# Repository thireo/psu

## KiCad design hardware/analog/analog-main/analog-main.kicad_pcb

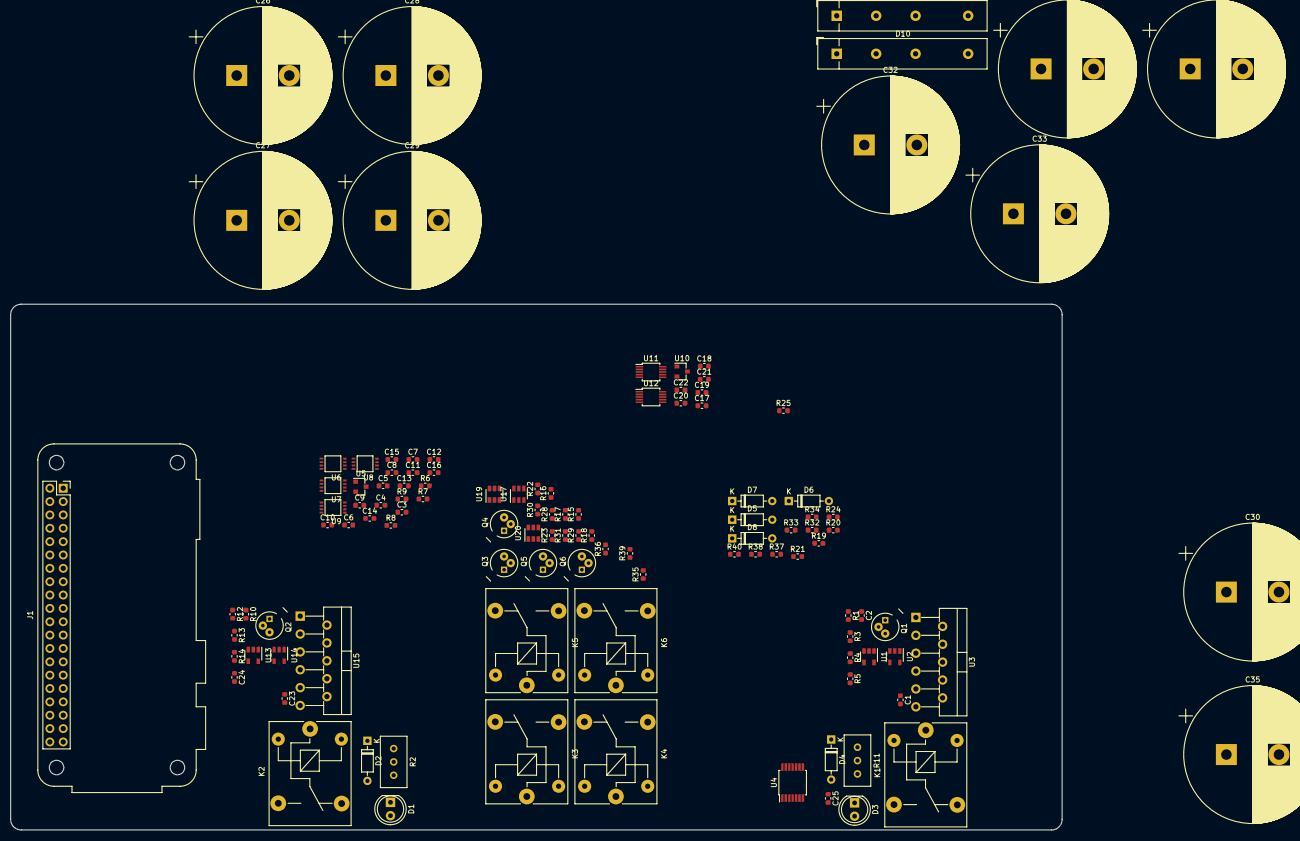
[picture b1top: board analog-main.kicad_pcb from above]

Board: 2 copper layers, 200.0 x 100.0 mm, 114 parts (0 on the bottom side), 61 nets, no tracks yet.

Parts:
C1, C2, C5, C8, C9, C10, C15, C16, C17, C18, C19, C20, C21, C22, C23, C24, C25: 100n; C_0603_1608Metric
C3, C4, C11, C12: 100n / 100p; C_0603_1608Metric
C6, C7, C13, C14: 4u7; C_0603_1608Metric
C26, C27, C28, C29, C30, C31, C32, C33, C34, C35: 4700u; CP_Radial_D26.0mm_P10.00mm_SnapIn
D1, D3: TEMP_LED; LED_D5.0mm
D2, D4, D5, D6, D7, D8: D_Zener; D_DO-35_SOD27_P7.62mm_Horizontal
D9, D10: D_Bridge_+-AA; Diode_Bridge_32.0x5.6x17.0mm_P10.0mm_P7.5mm
J1: Raspberry_Pi_2_3; Raspberry_Pi_Zero_Socketed_THT_FaceDown_MountingHoles
K1, K2, K3, K4, K5, K6: SANYOU_SRD_Form_C; Relay_SPDT_SANYOU_SRD_Series_Form_C
Q1, Q2, Q3, Q4, Q5, Q6: 2N2222; TO-18-3
R1, R4, R10, R13, R15, R17, R28, R30, R36, R39: 1k; R_0603_1608Metric
R2, R11: 10k POT; Potentiometer_Bourns_3296W_Vertical
R3, R12: >250; R_0603_1608Metric
R5, R6, R7, R8, R9, R14, R16, R18, R29, R31: 10k; R_0603_1608Metric
R19, R32: 100m 1%; R_0603_1608Metric
R20, R33: 5R 1%; R_0603_1608Metric
R21, R22, R34: 10k 1%; R_0603_1608Metric
R23, R25: 1k 1%; R_0603_1608Metric
R24: 33k 1%; R_0603_1608Metric
R35: 100R; R_0603_1608Metric
R37: 6k8 1%; R_0603_1608Metric
R38: 2k2 1%; R_0603_1608Metric
R40: 3k 1%; R_0603_1608Metric
U1, U2, U13, U14: LMV321; SOT-23-5
U3, U15: OPA549; TO-220-11_P3.4x5.08mm_StaggerOdd_Lead4.85mm_Vertical
U4: 74HCT04; TSSOP-14_4.4x5mm_P0.65mm
U5, U10: MCP1525-TT; SOT-23
U6, U7, U8, U9: MAX5216; uMAX8
U11, U12: MCP3301; MSOP-10_3x3mm_P0.5mm
U17, U19, U20: MAX4239AUT; SOT-23-6

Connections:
+1V8: C19.1, C21.1, U11.2, U12.2
+3V3: C20.1, C22.1, U11.10, U12.10
+4V: C10.1, U5.2, U6.1, U7.1, U8.1, U9.1
+5C: C1.1, C2.1, C6.1, C7.1, C8.2, C9.2, C13.1, C14.1, C15.2, C16.2, C23.1, C24.1, C25.1, U1.5, U2.5, U4.14, U6.7, U7.7, U8.7, U9.7, U13.5, U14.5, U17.6, U19.6, U20.6
+5V: C5.1, C17.1, D2.1, D4.1, D5.1, D6.1, D7.1, D8.1, K1.2, K2.2, K3.2, K4.2, K5.2, K6.2, U5.1, U10.1
+36V: U3.10, U3.11, U15.10, U15.11
-5V: U19.2, U20.2
/Analog to Digital/AIN0+: U11.3, U17.1
/Analog to Digital/AIN1+: R40.1, U12.3, U20.1
/Analog to Digital/MISO: U11.7, U12.7
/Analog to Digital/MOSI: U6.4, U7.4, U8.4, U9.4, U11.9, U12.9
/Analog to Digital/SCK: U6.3, U7.3, U8.3, U9.3, U11.8, U12.8
/Current Measurements/OUT_0+: K1.3, K3.1
/Current Measurements/OUT_1+: K2.3, K5.1
/Digital to Analog/DAC_OUT_0: U2.3, U2.4, U3.8, U7.6
/Digital to Analog/DAC_OUT_1: U1.3, U1.4, U3.4, U6.6
/Digital to Analog/DAC_OUT_2: U9.6, U14.3, U14.4, U15.8
/Digital to Analog/DAC_OUT_3: U8.6, U13.3, U13.4, U15.4
/Digital to Analog/~CLR_0: C4.2, R7.1, U7.5
/Digital to Analog/~CLR_1: C3.2, R6.1, U6.5
/Digital to Analog/~CLR_2: C12.2, R9.1, U9.5
/Digital to Analog/~CLR_3: C11.2, R8.1, U8.5
GND: C1.2, C2.2, C3.1, C4.1, C5.2, C6.2, C7.2, C8.1, C9.1, C10.2, C11.1, C12.1, C13.2, C14.2, C15.1, C16.1, C17.2, C18.2, C19.2, C20.2, C21.2, C22.2, C23.2, C24.2, C25.2, C26.2, C27.2, C28.2, C29.2, C30.2, C31.2, C32.2, C33.2, C34.2, C35.2, D1.1, D3.1, D9.2, D10.2, J1.6, J1.9, J1.14, J1.20, J1.25, J1.30, J1.34, J1.39, Q1.3, Q2.3, Q3.3, Q4.3, Q5.3, Q6.3, R1.1, R5.2, R6.2, R7.2, R8.2, R9.2, R10.1, R14.2, R16.2, R18.2, R19.1, R20.1, R21.1, R23.1, R25.1, R29.2, R31.2, R32.1, R33.1, R34.1, R36.1, R39.1, U1.1, U1.2, U2.1, U2.2, U3.5, U3.6, U3.7, U4.7, U5.3, U6.8, U7.8, U8.8, U9.8, U10.3, U11.4, U11.5, U12.4, U12.5, U13.1, U13.2, U14.1, U14.2, U15.5, U15.6, U15.7, U17.2
unnamed: C18.1, U10.2, U11.1, U12.1
unnamed: C26.1, C27.1, C28.1, C29.1, D9.1
unnamed: C30.1, K1.1, R2.2, U3.1, U3.2
unnamed: C31.1, C32.1, C33.1, C34.1, D10.1
unnamed: D1.2, R3.2
unnamed: D2.2, K1.5, Q1.1
unnamed: D3.2, R12.2
unnamed: D4.2, K2.5, Q2.1
unnamed: D5.2, K3.5, Q3.1
unnamed: D6.2, K4.5, Q4.1
unnamed: D7.2, K5.5, Q5.1
unnamed: D8.2, K6.5, Q6.1
unnamed: K2.1, R11.2, U15.1, U15.2
unnamed: K3.3, K3.4, K4.1, R19.2, R22.2
unnamed: K4.3, R21.2
unnamed: K4.4, R20.2
unnamed: K5.3, K5.4, K6.1, R32.2, R35.2
unnamed: K6.3, R34.2
unnamed: K6.4, R33.2
unnamed: Q1.2, R4.1, R5.1
unnamed: Q2.2, R13.1, R14.1
unnamed: Q3.2, R15.1, R16.1
unnamed: Q4.2, R17.1, R18.1
unnamed: Q5.2, R28.1, R29.1
unnamed: Q6.2, R30.1, R31.1
unnamed: R1.2, R2.1, U3.3
unnamed: R3.1, U4.2
unnamed: R10.2, R11.1, U15.3
unnamed: R12.1, U4.4
unnamed: R22.1, R25.2, U17.3
unnamed: R23.2, R24.2, U17.4
unnamed: R35.1, U19.3
unnamed: R36.2, R37.2, U19.4
unnamed: R37.1, R38.2
unnamed: R38.1, U19.1, U20.3
unnamed: R39.2, R40.2, U20.4
unnamed: U3.9, U4.1
unnamed: U4.3, U15.9

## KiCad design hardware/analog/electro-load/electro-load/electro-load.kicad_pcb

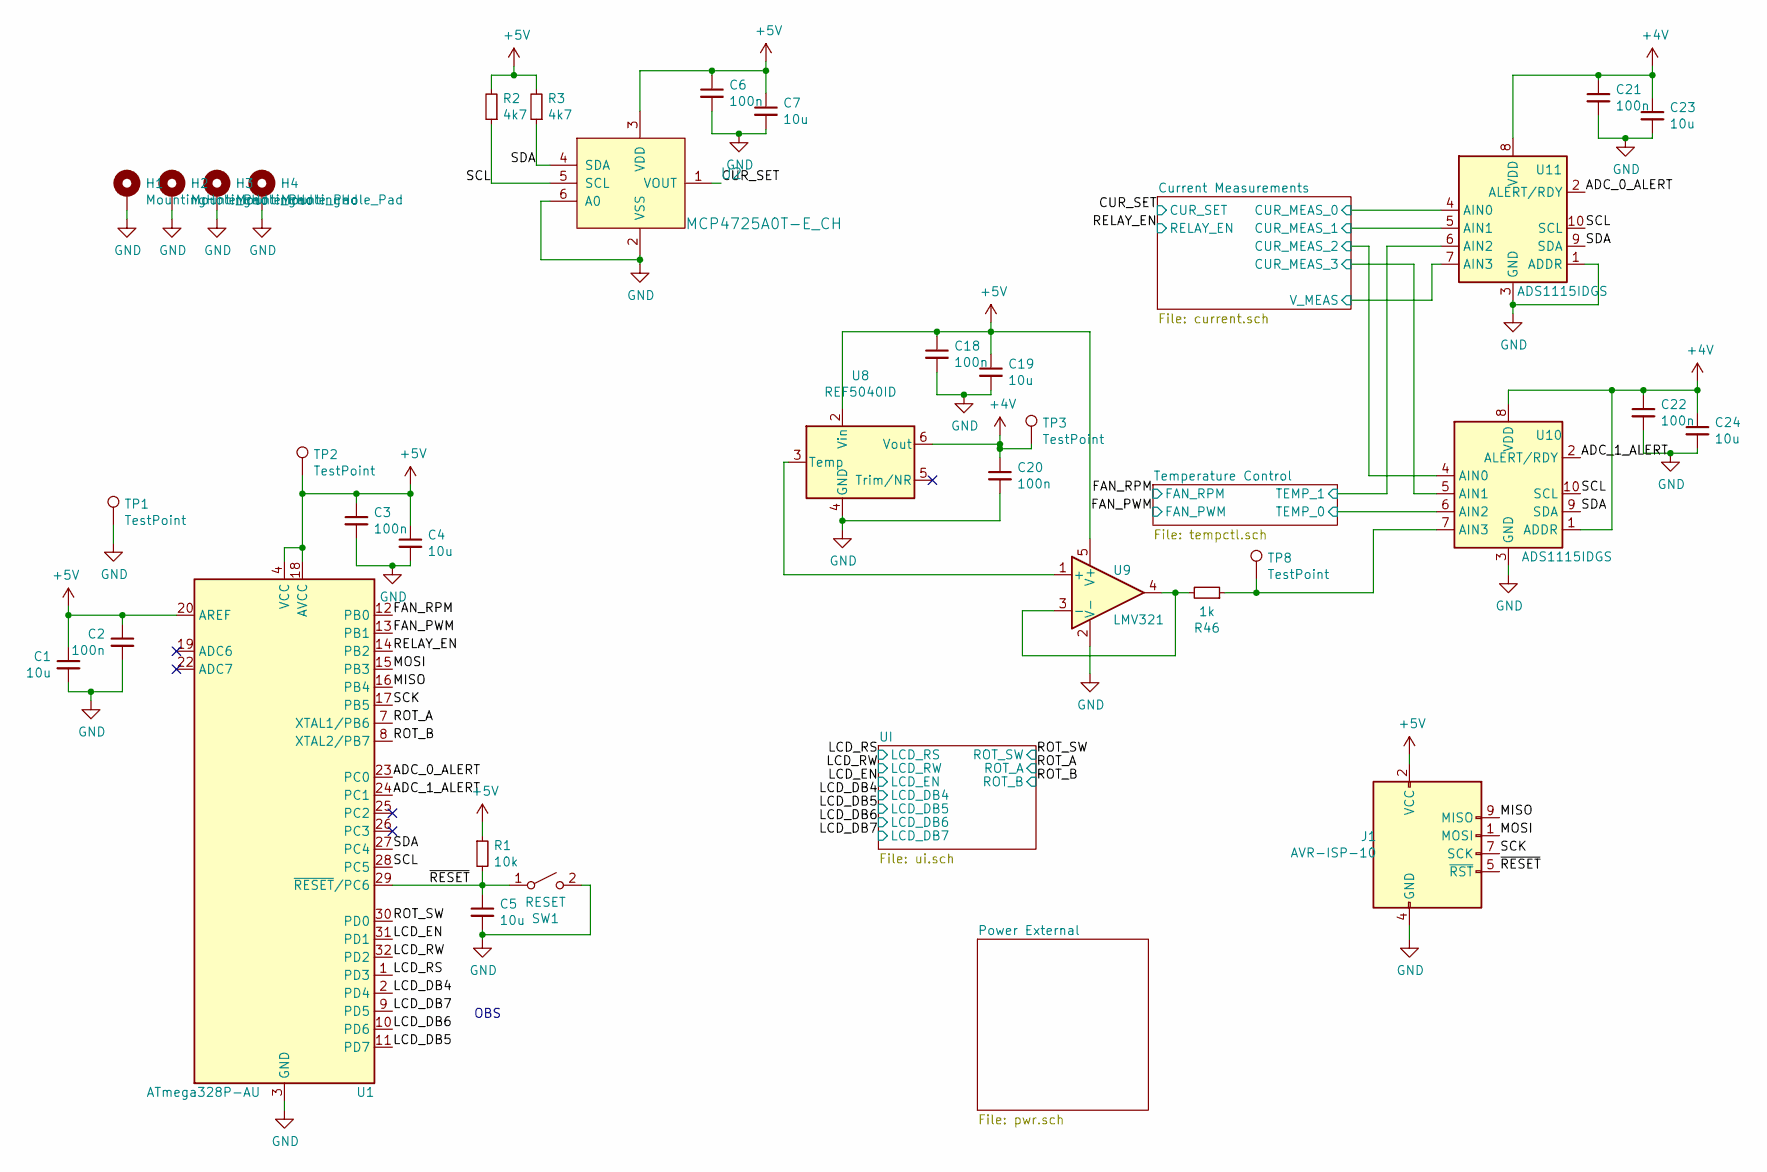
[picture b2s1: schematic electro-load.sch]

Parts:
C1, C4, C5, C7, C19, C23, C24: 10u; C_0603_1608Metric
C2, C3, C6, C18, C20, C21, C22: 100n; C_0603_1608Metric
H1, H2, H3, H4: MountingHole_Pad; MountingHole_3.2mm_M3_Pad_Via
J1: AVR-ISP-10; PinHeader_2x05_P2.54mm_Vertical
R1: 10k; R_0603_1608Metric
R2, R3: 4k7; R_0603_1608Metric
R46: 1k; R_0603_1608Metric
SW1: RESET; SW_PUSH_6mm_H4.3mm
TP1, TP2, TP3, TP8: TestPoint; testpoint_probe
U1: ATmega328P-AU; TQFP-32_7x7mm_P0.8mm
U2: MCP4725A0T-E_CH; SOT-23-6; MPN MCP4725A0T-E/CH; Digi-Key_PN MCP4725A0T-E/CHCT-ND
U8: REF5040ID; SOIC-8_3.9x4.9mm_P1.27mm
U9: LMV321; SOT-23-5
U10, U11: ADS1115IDGS; TSSOP-10_3x3mm_P0.5mm

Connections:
+4V: C20.1, C21.1, C22.1, C23.1, C24.1, TP3.1, U8.6 (Vout), U10.1 (ADDR), U10.8 (VDD), U11.8 (VDD)
/ADC_0_ALERT: U1.23 (PC0), U11.2 (ALERT/RDY)
/ADC_1_ALERT: U1.24 (PC1), U10.2 (ALERT/RDY)
/CUR_SET: U2.1 (VOUT); also elsewhere on the board
/Current Measurements/CUR_MEAS_0: U11.4 (AIN0); also elsewhere on the board
/Current Measurements/CUR_MEAS_1: U11.5 (AIN1); also elsewhere on the board
/Current Measurements/CUR_MEAS_2: U10.4 (AIN0); also elsewhere on the board
/Current Measurements/CUR_MEAS_3: U10.5 (AIN1); also elsewhere on the board
/Current Measurements/V_MEAS: U11.7 (AIN3); also elsewhere on the board
/FAN_PWM: U1.13 (PB1); also elsewhere on the board
/FAN_RPM: U1.12 (PB0); also elsewhere on the board
/LCD_DB4: U1.2 (PD4); also elsewhere on the board
/LCD_DB5: U1.11 (PD7); also elsewhere on the board
/LCD_DB6: U1.10 (PD6); also elsewhere on the board
/LCD_DB7: U1.9 (PD5); also elsewhere on the board
/LCD_EN: U1.31 (PD1); also elsewhere on the board
/LCD_RS: U1.1 (PD3); also elsewhere on the board
/LCD_RW: U1.32 (PD2); also elsewhere on the board
/MISO: J1.9 (MISO), U1.16 (PB4)
/MOSI: J1.1 (MOSI), U1.15 (PB3)
/RELAY_EN: U1.14 (PB2); also elsewhere on the board
/ROT_A: U1.7 (XTAL1/PB6); also elsewhere on the board
/ROT_B: U1.8 (XTAL2/PB7); also elsewhere on the board
/ROT_SW: U1.30 (PD0); also elsewhere on the board
/SCK: J1.7 (SCK), U1.17 (PB5)
/SCL: R2.1, U1.28 (PC5), U2.5 (SCL), U10.10 (SCL), U11.10 (SCL)
/SDA: R3.1, U1.27 (PC4), U2.4 (SDA), U10.9 (SDA), U11.9 (SDA)
/Temperature Control/TEMP_0: U10.6 (AIN2); also elsewhere on the board
/Temperature Control/TEMP_1: U11.6 (AIN2); also elsewhere on the board
/~RESET: C5.1, J1.5 (~RST), R1.2, SW1.1 (A), U1.29 (~RESET~/PC6)
GND: C1.2, C2.2, C3.2, C4.2, C5.2, C6.2, C7.2, C18.2, C19.2, C20.2, C21.2, C22.2, C23.2, C24.2, H1.1, H2.1, H3.1, H4.1, J1.4 (GND), J1.6 (GND), J1.8 (GND), J1.10 (GND), SW1.2 (B), TP1.1, U1.3 (GND), U1.5 (GND), U1.21 (GND), U2.2 (VSS), U2.6 (A0), U8.4 (GND), U9.2 (V-), U10.3 (GND), U11.1 (ADDR), U11.3 (GND); also elsewhere on the board
unnamed: R46.1, TP8.1, U10.7 (AIN3)
unnamed: R46.2, U9.3 (-), U9.4
unnamed: U8.3 (Temp), U9.1 (+)

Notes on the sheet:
OBS

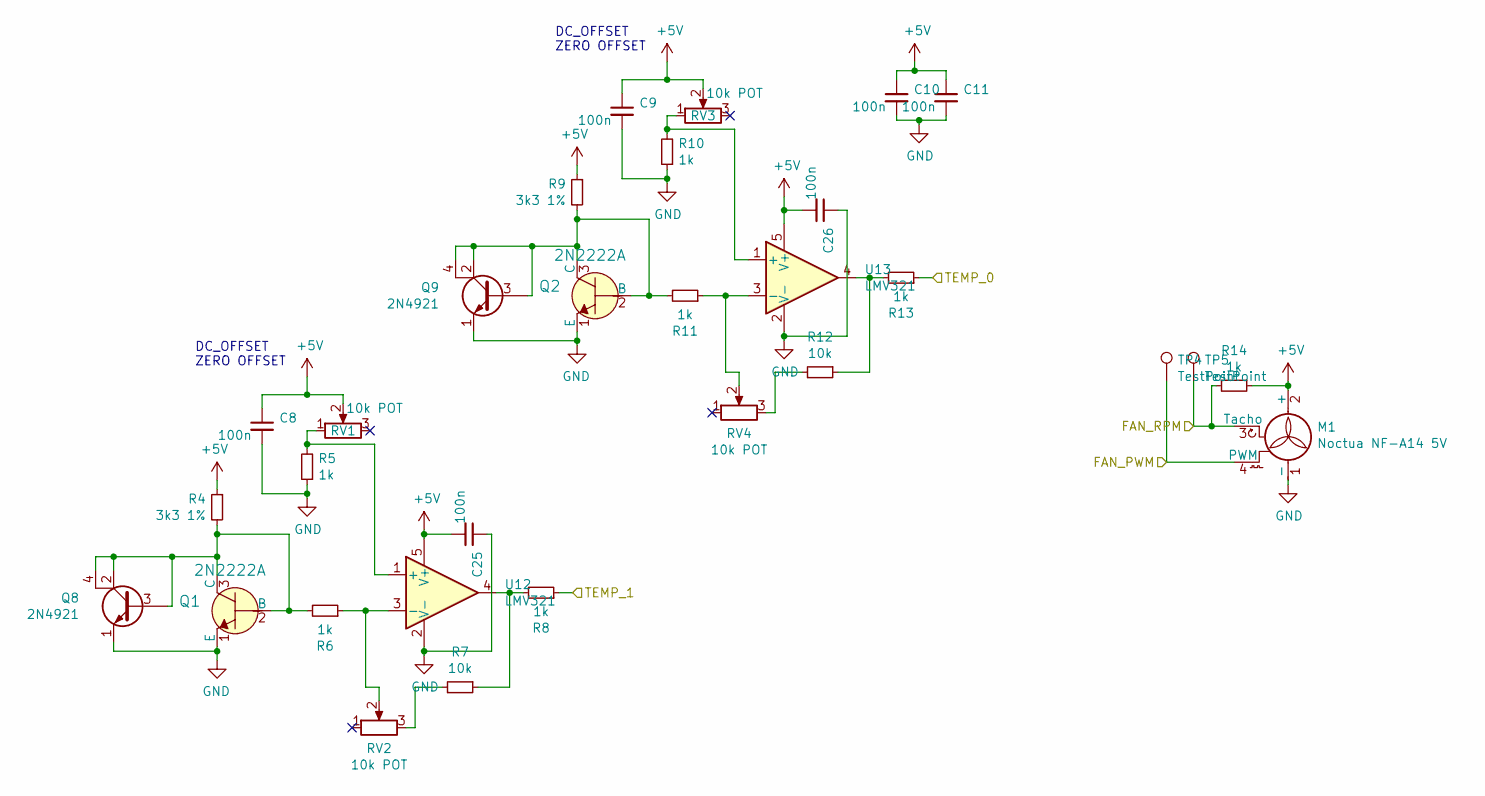
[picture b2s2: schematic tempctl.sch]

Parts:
C8, C9, C10, C11, C25, C26: 100n; C_0603_1608Metric
M1: Noctua NF-A14 5V; PinHeader_1x04_P2.54mm_Vertical
Q1, Q2: 2N2222A; TO-92_Inline; MPN 2N2222A; Digi-Key_PN 2N2222ACS-ND
Q8, Q9: 2N4921; TO-126-3_Vertical
R4, R9: 3k3 1%; R_0603_1608Metric
R5, R6, R8, R10, R11, R13, R14: 1k; R_0603_1608Metric
R7, R12: 10k; R_0603_1608Metric
RV1, RV2, RV3, RV4: 10k POT; Potentiometer_Bourns_3296W_Vertical
TP4, TP5: TestPoint; testpoint_probe
U12, U13: LMV321; SOT-23-5

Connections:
/FAN_PWM: M1.4 (PWM), TP4.1; also elsewhere on the board
/FAN_RPM: M1.3 (Tacho), R14.2, TP5.1; also elsewhere on the board
/Temperature Control/TEMP_0: R13.1; also elsewhere on the board
/Temperature Control/TEMP_1: R8.1; also elsewhere on the board
GND: C8.2, C9.2, C10.2, C11.2, C25.1, C26.1, M1.1 (-), Q1.1 (E), Q2.1 (E), Q8.1 (E), Q9.1 (E), R5.1, R10.1, U12.2 (V-), U13.2 (V-); also elsewhere on the board
unnamed: Q1.2 (B), Q1.3 (C), Q8.2 (C), Q8.3 (B), Q8.4 (C), R4.2, R6.2
unnamed: Q2.2 (B), Q2.3 (C), Q9.2 (C), Q9.3 (B), Q9.4 (C), R9.2, R11.2
unnamed: R5.2, RV1.1, U12.1 (+)
unnamed: R6.1, RV2.2, U12.3 (-)
unnamed: R7.1, R8.2, U12.4
unnamed: R7.2, RV2.3
unnamed: R10.2, RV3.1, U13.1 (+)
unnamed: R11.1, RV4.2, U13.3 (-)
unnamed: R12.1, R13.2, U13.4
unnamed: R12.2, RV4.3

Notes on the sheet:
DC_OFFSET ZERO OFFSET

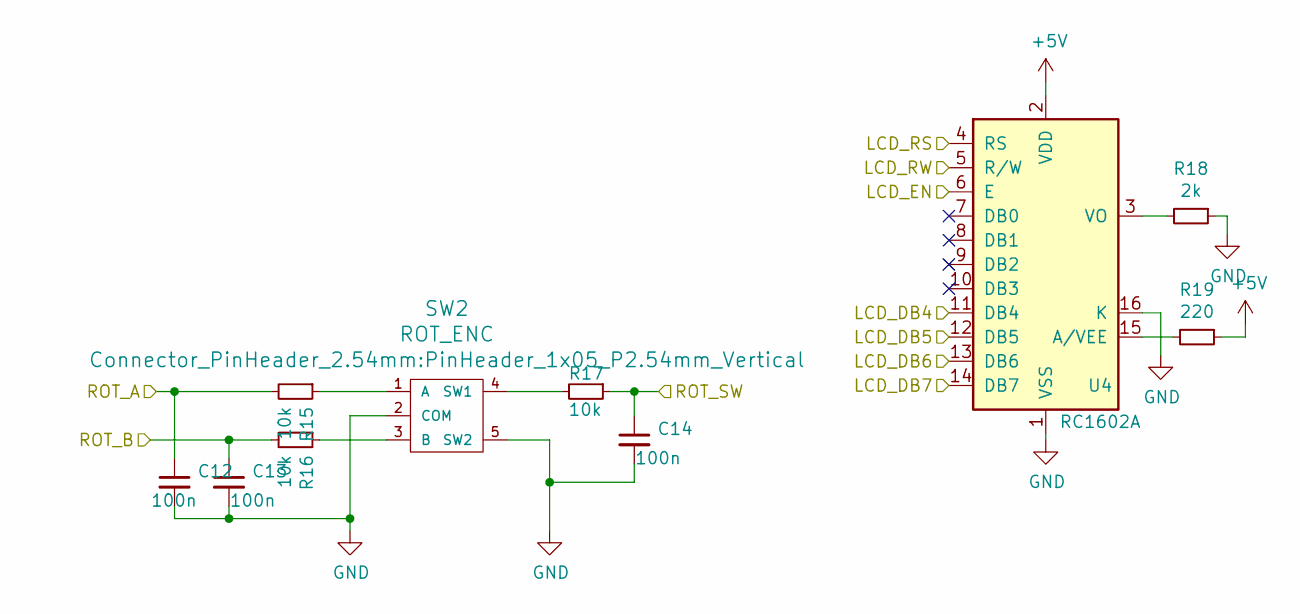
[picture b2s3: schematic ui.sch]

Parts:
C12, C13, C14: 100n; C_0603_1608Metric
R15, R16, R17: 10k; R_0603_1608Metric
R18: 2k; R_0603_1608Metric
R19: 220; R_0603_1608Metric
SW2: ROT_ENC; PinHeader_1x05_P2.54mm_Vertical
U4: RC1602A; PinHeader_1x16_P2.54mm_Vertical

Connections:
/LCD_DB4: U4.11 (DB4); also elsewhere on the board
/LCD_DB5: U4.12 (DB5); also elsewhere on the board
/LCD_DB6: U4.13 (DB6); also elsewhere on the board
/LCD_DB7: U4.14 (DB7); also elsewhere on the board
/LCD_EN: U4.6 (E); also elsewhere on the board
/LCD_RS: U4.4 (RS); also elsewhere on the board
/LCD_RW: U4.5 (R/W); also elsewhere on the board
/ROT_A: C12.1, R15.2; also elsewhere on the board
/ROT_B: C13.1, R16.2; also elsewhere on the board
/ROT_SW: C14.1, R17.1; also elsewhere on the board
GND: C12.2, C13.2, C14.2, R18.1, SW2.2 (COM), SW2.5 (SW2), U4.1 (VSS), U4.16 (K); also elsewhere on the board
unnamed: R15.1, SW2.1 (A)
unnamed: R16.1, SW2.3 (B)
unnamed: R17.2, SW2.4 (SW1)
unnamed: R18.2, U4.3 (VO)
unnamed: R19.2, U4.15 (A/VEE)

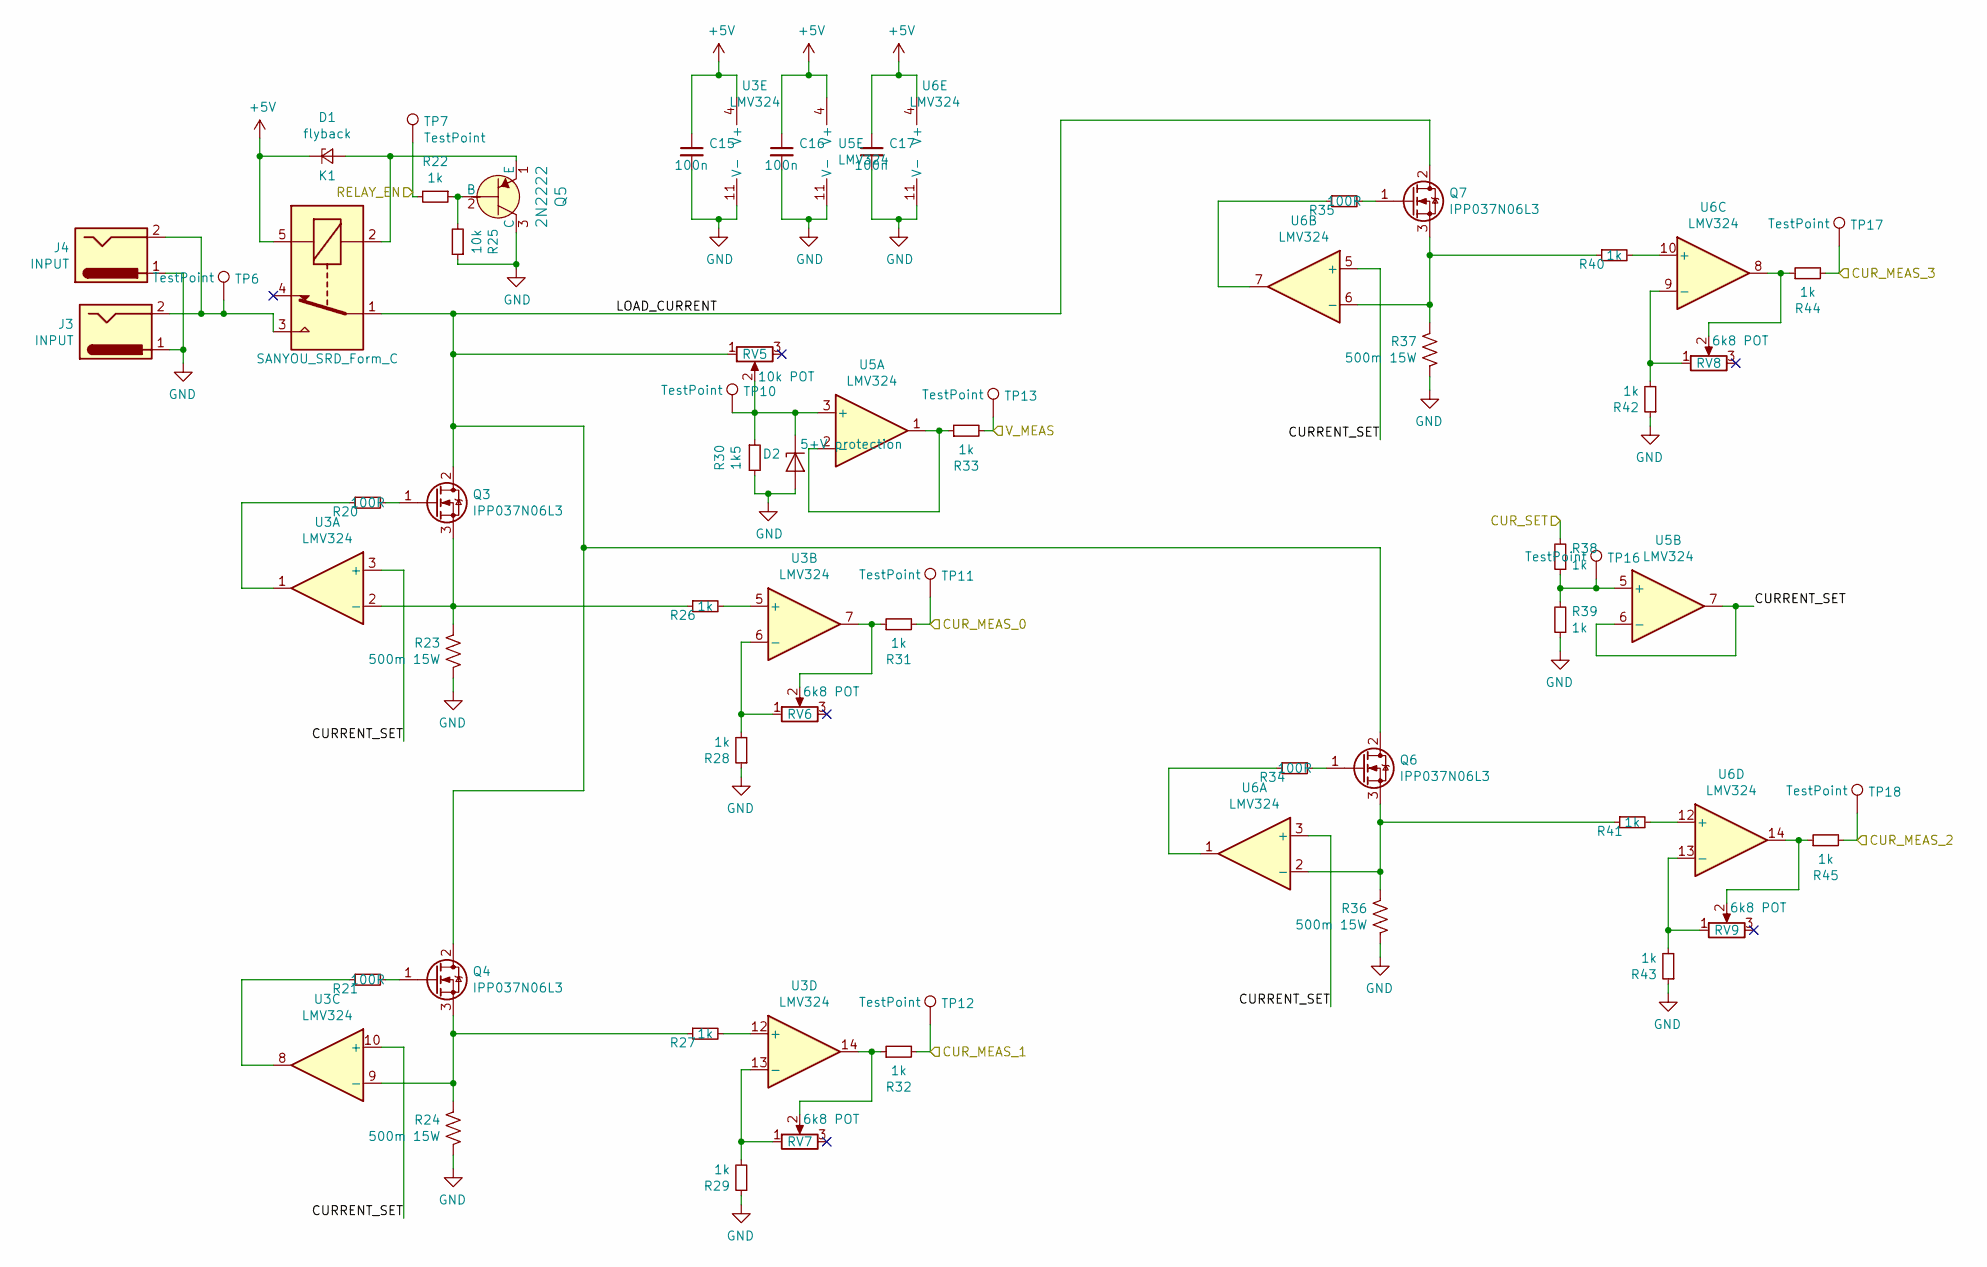
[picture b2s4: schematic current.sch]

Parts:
C15, C16, C17: 100n; C_0603_1608Metric
D1: flyback; D_DO-35_SOD27_P7.62mm_Horizontal
D2: 5+V protection; D_DO-35_SOD27_P7.62mm_Horizontal
J3, J4: INPUT; TestPoint_2Pads_Pitch5.08mm_Drill1.3mm
K1: SANYOU_SRD_Form_C; Relay_SPDT_SANYOU_SRD_Series_Form_C
Q3, Q4, Q6, Q7: IPP037N06L3; TO-220-3_Vertical
Q5: 2N2222; TO-92_Inline; MPN 2N2222; Digi-Key_PN 2N2222CS-ND
R20, R21, R34, R35: 100R; R_0603_1608Metric
R22, R26, R27, R28, R29, R31, R32, R33, R38, R39, R40, R41, R42, R43, R44, R45: 1k; R_0603_1608Metric
R23, R24, R36, R37: 500m 15W; TestPoint_2Pads_Pitch5.08mm_Drill1.3mm
R25: 10k; R_0603_1608Metric
R30: 1k5; R_0603_1608Metric
RV5: 10k POT; Potentiometer_Bourns_3296W_Vertical
RV6, RV7, RV8, RV9: 6k8 POT; Potentiometer_Bourns_3296W_Vertical
TP6, TP7, TP10, TP11, TP12, TP13, TP16, TP17, TP18: TestPoint; testpoint_probe
U3, U5, U6: LMV324; SOIC-14_3.9x8.7mm_P1.27mm

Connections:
/CUR_SET: R38.2; also elsewhere on the board
/Current Measurements/CURRENT_SET: U3.3 (+), U3.10 (+), U5.6 (-), U5.7, U6.3 (+), U6.5 (+)
/Current Measurements/CUR_MEAS_0: R31.2, TP11.1; also elsewhere on the board
/Current Measurements/CUR_MEAS_1: R32.2, TP12.1; also elsewhere on the board
/Current Measurements/CUR_MEAS_2: R45.2, TP18.1; also elsewhere on the board
/Current Measurements/CUR_MEAS_3: R44.2, TP17.1; also elsewhere on the board
/Current Measurements/LOAD_CURRENT: K1.1, Q3.2 (D), Q4.2 (D), Q6.2 (D), Q7.2 (D), RV5.1
/Current Measurements/V_MEAS: R33.2, TP13.1; also elsewhere on the board
/RELAY_EN: R22.2, TP7.1; also elsewhere on the board
GND: C15.2, C16.2, C17.2, D2.2 (A), J3.1, J4.1, Q5.3 (C), R23.2, R24.2, R25.1, R28.1, R29.1, R30.2, R36.2, R37.2, R39.1, R42.1, R43.1, U3.11 (V-), U5.11 (V-), U6.11 (V-); also elsewhere on the board
unnamed: D1.2 (A), K1.2, Q5.1 (E)
unnamed: D2.1 (K), R30.1, RV5.2, TP10.1, U5.3 (+)
unnamed: J3.2, J4.2, K1.3, TP6.1
unnamed: Q3.1 (G), R20.2
unnamed: Q3.3 (S), R23.1, R26.1, U3.2 (-)
unnamed: Q4.1 (G), R21.2
unnamed: Q4.3 (S), R24.1, R27.1, U3.9 (-)
unnamed: Q5.2 (B), R22.1, R25.2
unnamed: Q6.1 (G), R34.2
unnamed: Q6.3 (S), R36.1, R41.1, U6.2 (-)
unnamed: Q7.1 (G), R35.2
unnamed: Q7.3 (S), R37.1, R40.1, U6.6 (-)
unnamed: R20.1, U3.1
unnamed: R21.1, U3.8
unnamed: R26.2, U3.5 (+)
unnamed: R27.2, U3.12 (+)
unnamed: R28.2, RV6.1, U3.6 (-)
unnamed: R29.2, RV7.1, U3.13 (-)
unnamed: R31.1, RV6.2, U3.7
unnamed: R32.1, RV7.2, U3.14
unnamed: R33.1, U5.1, U5.2 (-)
unnamed: R34.1, U6.1
unnamed: R35.1, U6.7
unnamed: R38.1, R39.2, TP16.1, U5.5 (+)
unnamed: R40.2, U6.10 (+)
unnamed: R41.2, U6.12 (+)
unnamed: R42.2, RV8.1, U6.9 (-)
unnamed: R43.2, RV9.1, U6.13 (-)
unnamed: R44.1, RV8.2, U6.8
unnamed: R45.1, RV9.2, U6.14

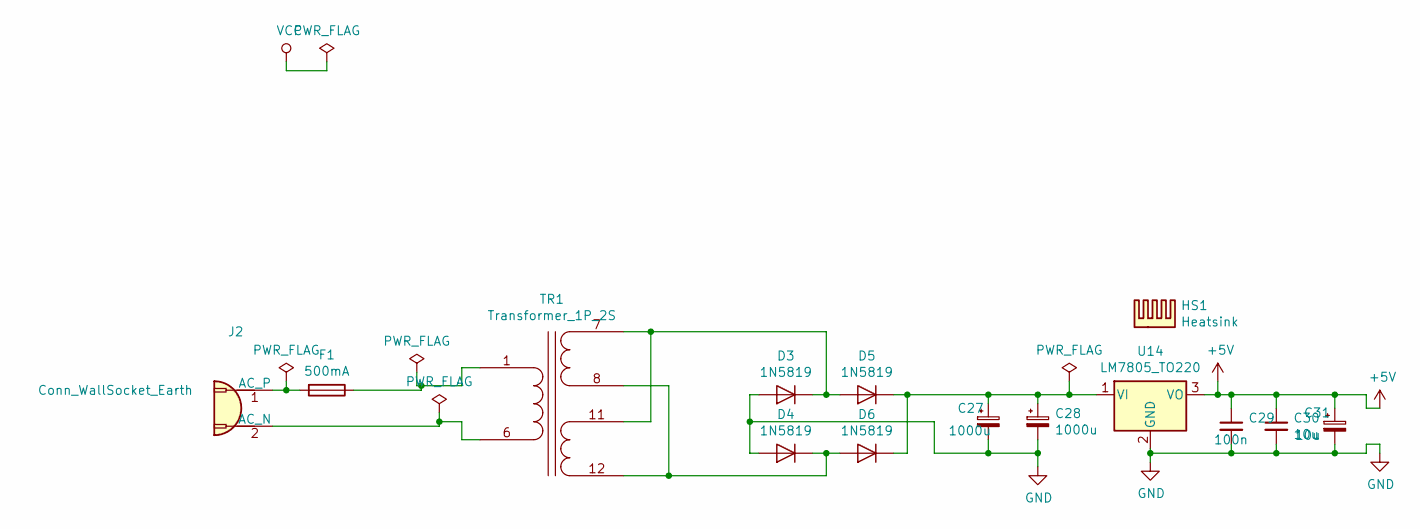
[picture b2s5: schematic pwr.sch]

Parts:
C1: 10u; CP_Radial_D6.3mm_P2.50mm
C8, C9: 1000u; CP_Radial_D10.0mm_P5.00mm
C29: 100n; C_0603_1608Metric
C30: 10u; C_0805_2012Metric
D3, D4, D5, D6: 1N5819; D_DO-41_SOD81_P7.62mm_Horizontal
F1: 500mA; KK-Fuseholder
HS1: Heatsink; Heatsink_Fischer_SK104-STC-STIC_35x13mm_2xDrill2.5mm
J2: Conn_WallSocket_Earth; Molex-KK-396-5277
TR1: Transformer_1P_2S; Transformer_Breve_TEZ-44x52
U14: LM7805_TO220; TO-220-3_Vertical

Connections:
GND: C1.2, C8.2, C9.2, C29.2, C30.2, D3.2 (A), D4.2 (A), U14.2 (GND); also elsewhere on the board
unnamed: D3.1 (K), D5.2 (A), TR1.7 (SA), TR1.11 (SC)
unnamed: D4.1 (K), D6.2 (A), TR1.8 (SB), TR1.12 (SD)
unnamed: F1.1, TR1.1 (AA)
unnamed: F1.2, J2.1 (AC_P)
unnamed: J2.2 (AC_N), TR1.6 (AB)

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
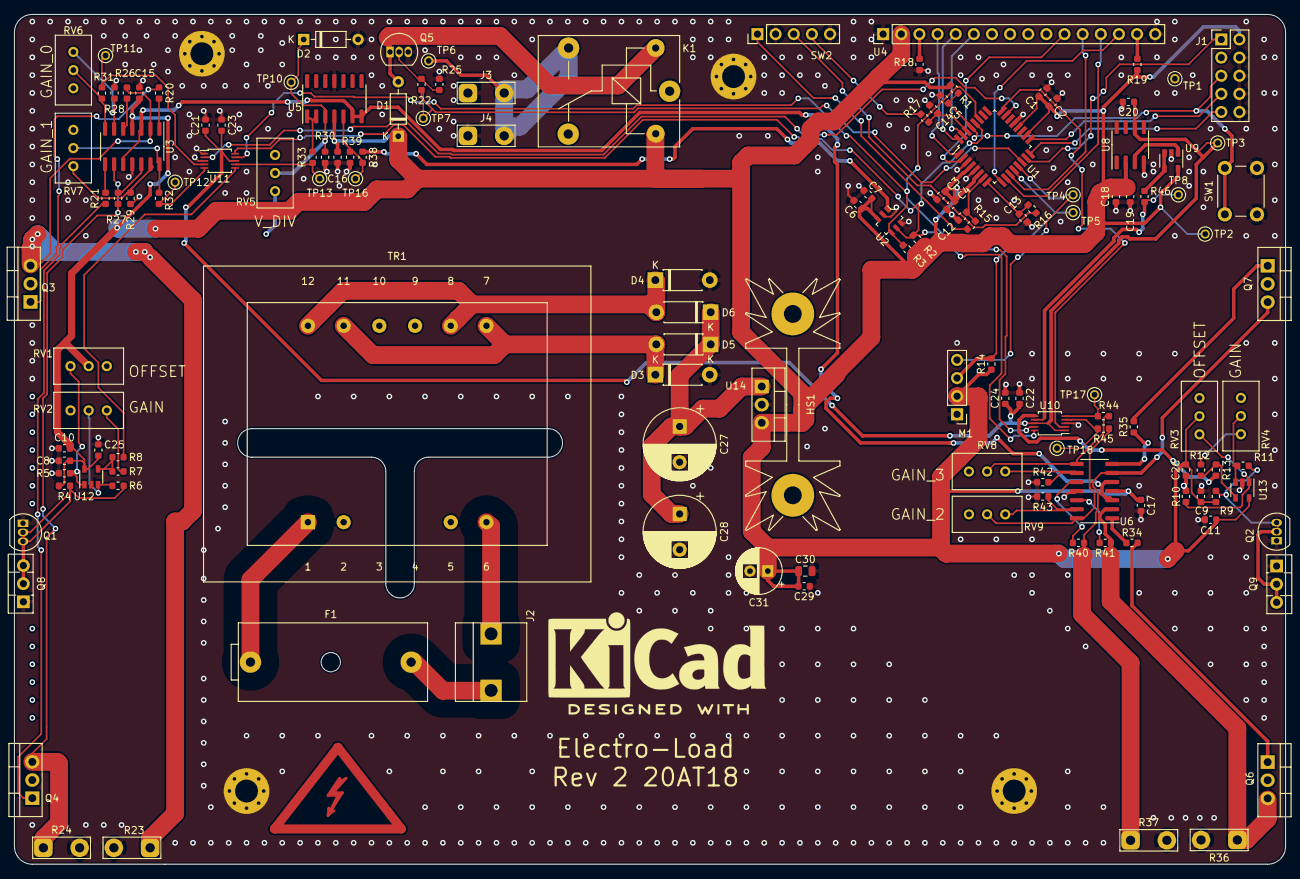
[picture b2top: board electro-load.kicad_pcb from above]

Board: 2 copper layers, 178.0 x 119.0 mm, 144 parts (0 on the bottom side), 88 nets.

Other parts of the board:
C27, C28: 1000u; CP_Radial_D10.0mm_P5.00mm
C31: 10u; CP_Radial_D6.3mm_P2.50mm

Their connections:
GND: C27.2, C28.2, C31.2; also elsewhere on the board

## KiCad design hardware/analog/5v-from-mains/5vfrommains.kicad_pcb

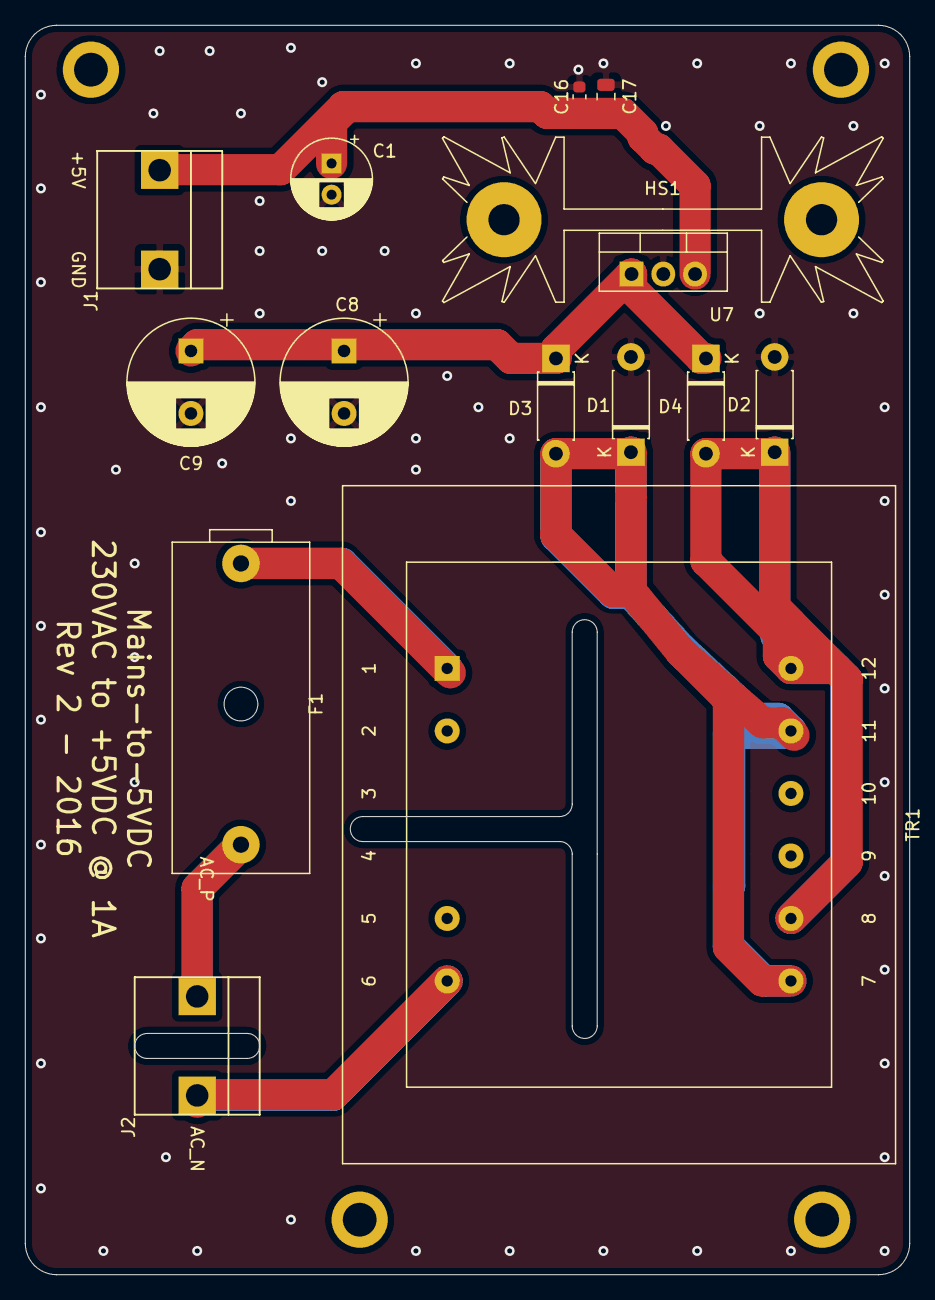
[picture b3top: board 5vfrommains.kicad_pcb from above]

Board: 2 copper layers, 70.8 x 100.0 mm, 15 parts (0 on the bottom side), 8 nets.

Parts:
C1: 10u; CP_Radial_D6.3mm_P2.50mm
C8, C9: 1000u; CP_Radial_D10.0mm_P5.00mm
C16: 100n; C_0603_1608Metric
C17: 10u; C_0805_2012Metric
D1, D2, D3, D4: 1N5819; D_DO-41_SOD81_P7.62mm_Horizontal
F1: 500mA; KK-Fuseholder
HS1: Heatsink; Heatsink_Fischer_SK104-STC-STIC_35x13mm_2xDrill2.5mm
J1, J2: Conn_WallSocket_Earth; Molex-KK-396-5277
TR1: Transformer_1P_2S; Transformer_Breve_TEZ-44x52
U7: LM7805_TO220; TO-220-3_Vertical

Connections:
+5V: C1.1, C16.1, C17.1, J1.1, U7.3
GND: C1.2, C8.2, C9.2, C16.2, C17.2, D1.2, D2.2, J1.2, U7.2
unnamed: C8.1, C9.1, D3.1, D4.1, U7.1
unnamed: D1.1, D3.2, TR1.7, TR1.11
unnamed: D2.1, D4.2, TR1.8, TR1.12
unnamed: F1.1, TR1.1
unnamed: F1.2, J2.1
unnamed: J2.2, TR1.6

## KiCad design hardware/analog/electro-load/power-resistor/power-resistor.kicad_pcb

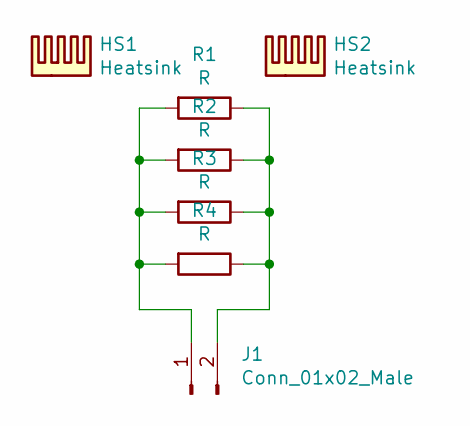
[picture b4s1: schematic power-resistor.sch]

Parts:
HS1, HS2: Heatsink; Heatsink_Fischer_SK104-STC-STIC_35x13mm_2xDrill2.5mm
J1: Conn_01x02_Male; 230VAC_PLUG
R1, R2, R3, R4: R; TO-220-2_Vertical

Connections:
unnamed: J1.1, R1.2, R2.2, R3.2, R4.2
unnamed: J1.2, R1.1, R2.1, R3.1, R4.1

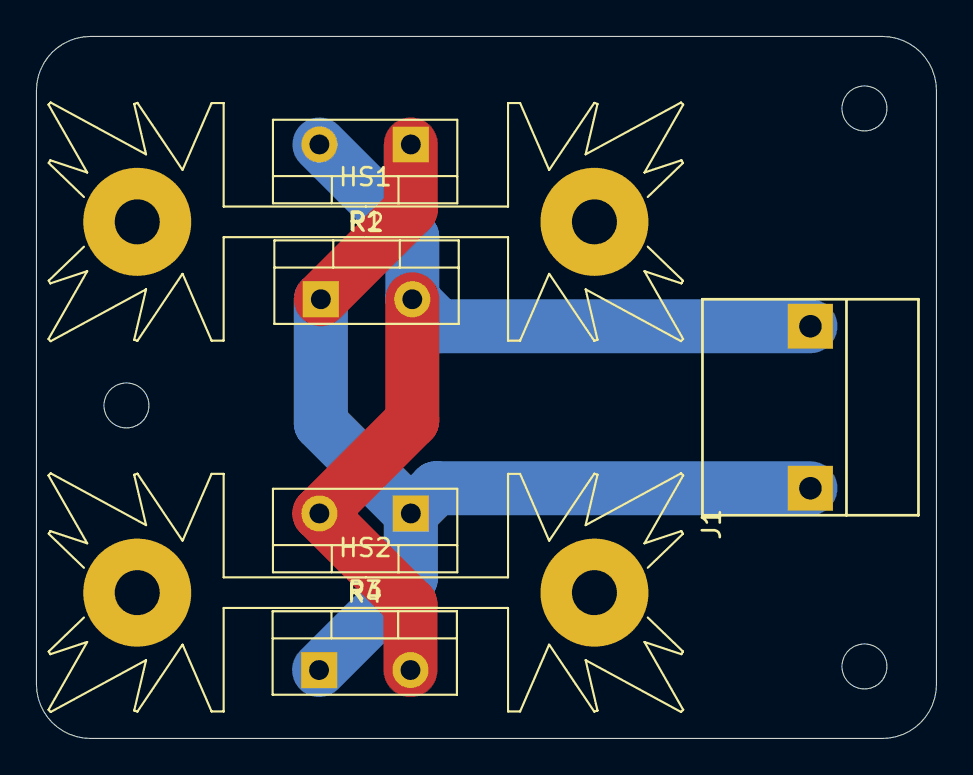
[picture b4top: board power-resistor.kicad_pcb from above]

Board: 2 copper layers, 50.0 x 39.0 mm, 7 parts (0 on the bottom side), 2 nets.

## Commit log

2019-12-20 Initial HW commit
2020-03-17 Added simulation for electronic-load
2020-03-17 Added datasheets for use with electronic load
2020-03-17 Added start of electronic load kicad project
2020-03-21 Added datasheets for noctua fan, mcu and lm358 etc.
    Finished schematic rev 1 of electro load
2020-03-23 Added inverting opamp config. for 2n2222 as temp sensor
    Fixed electro-load circuit to only need 5V and not close to DUT voltage.
2020-03-23 Spread schematic out into multiple subsheets. Removed LEDs as pins was needed for 16x2 display
2020-04-11 HW rev 1 of electronic load PCB.
2020-04-11 Added HW rev 1 of 5V from mains power - Previously combined with electroload
2020-04-11 Started work on Analog Main (Power Supply) board
2020-04-11 Added datasheets for new MOSFET. Previous MOSFET in electroload is not able to withstand power needed for 8A.
2020-04-11 Simulations for transformer calculations - both 5V and PSU
2020-04-11 Added simulations for electronic load rev 2, OPA549 lib and regulators
2020-04-18 Added voltage reference REF5020 datasheet
    Started work on HW rev 2 of electro load and 5v-from-mains - rev 1 contained misaligned footprints.
2020-04-20 Arranged mosfets and temperature probes to amplifier casing.
    Added Power schematic from 5v-from-mains
2020-04-21 Added basic 3D model of amplifier encasing
2020-04-21 Added blender file and x3d file for amplifer encasing
2020-04-23 Changed pin connections to/from lmv324 in order to avoid bird nesting. Widened traces for 5V and LOAD_CURRENT. Added four power resistors to the fab layer. Arranged left side analogs
2020-04-24 All traces layed out. Silkscreen and finishing touches needed.
2020-04-25 Fixed silkscreen and slighty widened load_current trace.
2020-04-25 Fixed missing GND trace on SAMD21
2020-04-25 Added mounting holes and added silkscreen text for V_DIV
2020-04-25 Added extra footprints for temperature probes - 2N4921
2020-04-25 Added mounting holes to schematic as well. Also made them solid ground anchors.
2020-04-29 Applied fixed symbol for OPA549
    Configured all footprints
2020-04-30 Changed OPA549 simulation symbol to the autogenerated one used in trafo-calc simulations
2020-04-30 Fixed bug in OPA549. Symbol should not refer to SPICE model in schematic
2020-05-17 Initial commit of software for Electroload
    Working relay function, PWM Fan control working maybe
2020-05-18 working PWM, however not tested with Noctua 5V PWM fan yet
2020-05-18 Actually working PWM control of fan. WGM10-11 should be configured at TCCR1A and WGM12-13 at TCCR1B
2020-05-22 I2C read of MCP device seems to be working.
    Back to basic embedded C
2020-05-22 Fixed i2c addresses for ADS1115s. 0x90 and 0x92
2020-05-22 Added adc_init function with test of ADS1115 readbacks.
2020-05-24 Added i2c functions from peter fleury
    Working DAC (MCP4725) fast write function
2020-05-24 Added interrupt service routine for ADS0 and ADS1 conversion ready
2020-08-21 Sorry future me
2020-11-22 Fixed compilations errors for implicit declarations of adc lib. Cleaned main.c and moved includes to main.h. Added optimization and definition of mcu
2020-11-23 working makefile
2020-11-23 Fixed makefile bug with clean rule. Default is all. Added working vscodes
2020-11-23 Fully functioning c_cpp_properties file.
2020-11-26 Changed c_cpp_prop to two separate configs for OS.
2020-11-26 Fixed lct_set_line to support all four lines.
2020-11-26 Added continous ADC readings.
2020-11-27 Moved vscode files to encasingcontroller folder. Fixed double definition of __AVR_ATMEGA328P__. Fixed paths for Windows config. Fixed intellisensemode for windows config.
2020-11-27 Fixed unfinished business in adc_start_conversion.
2020-11-27 Removed flags from main.h. Not needed due to proper vscode config.
2020-11-27 Fixed missing declaration of i2c_readnack. Fixed incompatible pointer warnings for sprintf.
2021-01-01 Revised makefile
    Updated to accommodate vscode
2021-01-07 Revised tasks.json.
2021-01-20 Working version of makefile and F_CPU definition.
    Tested on linux
2021-01-20 Added C output files to gitignore
2021-01-20 Added LCD output of all 8 ADC readings. Corrected signedness
2021-01-20 Changed all ADC inputs to relative to GND
2021-01-20 Added Flash to tasks.json
2021-08-10 Added vscode workspace settings.
2021-08-10 Added makefile and flashing script.
2021-10-07 Added tool path to makefile, in order to hopefully support vscodes repo.
2021-10-15 Changed compiler path in c_cpp_propertiers to avr specific.
2021-10-15 minor formatting
2021-10-15 Added new local gitignore for software encasingcontroller.
2021-10-15 intentional breakage of main.c
2021-10-15 New intentional breakage. pre commit hook test.
2021-10-19 Finished fucking around
2021-10-19 Fixed warning for useless statements
2021-10-19 Added -Wextra to makefile
2021-10-22 Working makefile using docker container with debian installed
2021-10-25 Working makefile. Works on linux, via docker container.
2021-10-25 Added docker pre-commit shell script.
2021-11-18 Working temperature measurements in SW. Working makefile.
2021-11-18 Working vscode settings.
